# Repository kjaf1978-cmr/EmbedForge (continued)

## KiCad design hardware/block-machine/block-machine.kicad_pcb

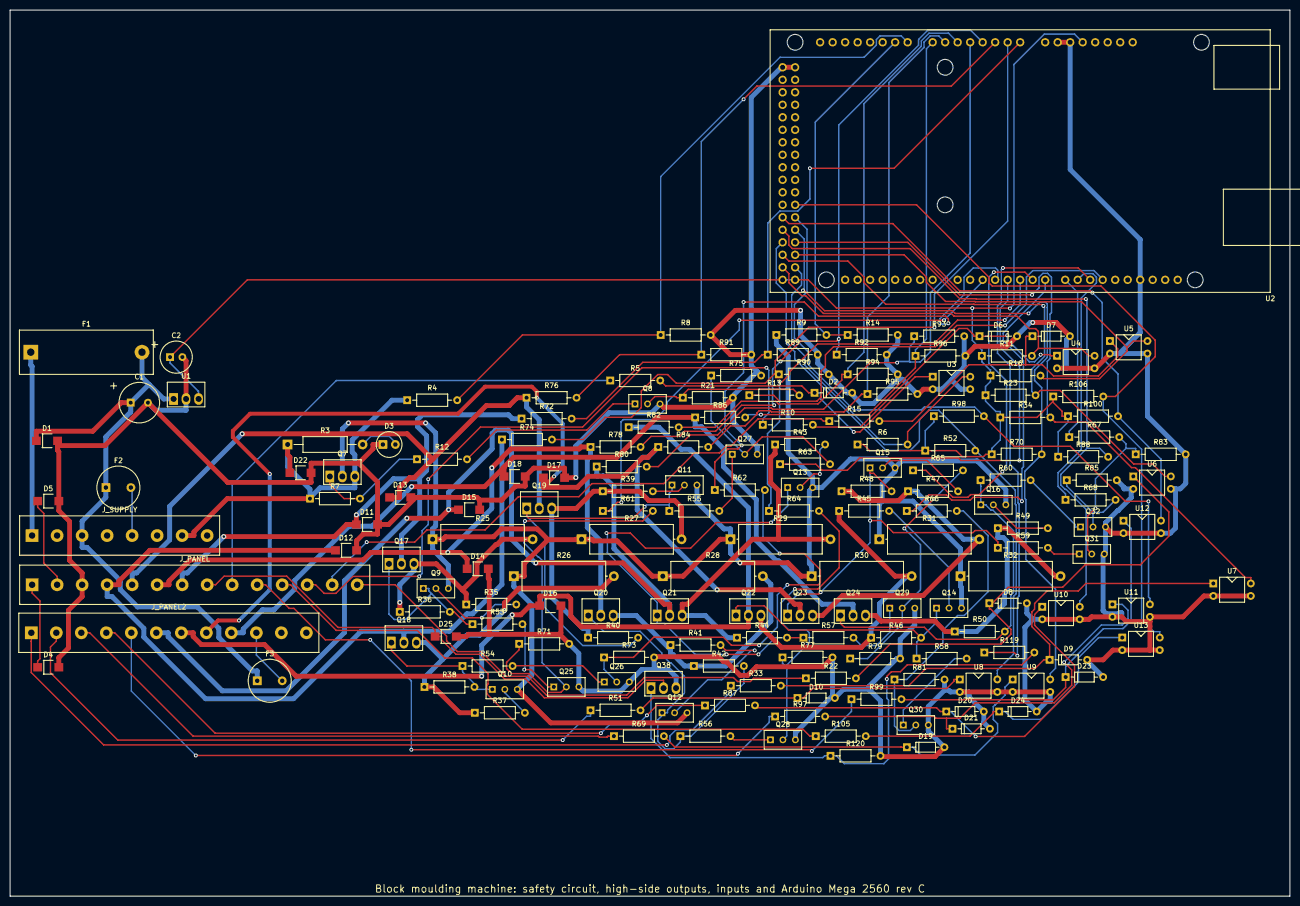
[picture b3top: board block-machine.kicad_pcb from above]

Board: 2 copper layers, 260.0 x 180.0 mm, 170 parts (0 on the bottom side), 117 nets.

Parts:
C1: 22u; CP_Radial_D8
C2: 22u; CP_Radial_D6.3
D1, D25: SMAJ33A; D_SMA
D2, D6, D7, D8, D9, D10, D19, D20, D21, D23, D24: 1N4148; D_DO-35
D3: green; LED_D5.0
D4, D5, D11, D12, D13, D14, D15, D16, D17, D18, D22: SMAJ33CA; D_SMA
F1: 8; Fuseholder_5x20
F2: 2; F_TR5
F3: 1; F_TR5
J_PANEL: to the panel; TerminalBlock_1x14
J_PANEL2: to the panel; TerminalBlock_1x12
J_SUPPLY: supplies to the panel; TerminalBlock_1x8
Q7: IRF4905; TO-220_Vertical
Q8, Q25, Q26, Q27, Q28, Q29, Q30, Q31, Q32: BC547B; TO-92_Wide
Q9, Q10, Q11, Q12, Q13, Q14, Q15, Q16: BC557B; TO-92_Wide
Q17, Q18, Q19, Q20, Q21, Q22, Q23, Q24: IRF9540N; TO-220_Vertical
Q38: IRLZ44N; TO-220_Vertical
R3: 2.2k; R_Axial_0309
R4, R9, R21, R71, R72, R73, R74, R75, R76, R77, R78, R79, R80, R81, R82, R83, R84, R85, R86: 47k; R_Axial_0207
R5, R10, R15, R22, R33, R51, R69, R87, R97, R99, R105: 4.7k; R_Axial_0207
R6, R7, R8, R11, R12, R13, R14, R16, R23, R34, R36, R38, R40, R42, R44, R46, R48, R50, R52, R53, R54, R55, R56, R57, R58, R59, R60, R61, R62, R63, R64, R65, R66, R67, R68, R70, R88, R89, R90, R91, R92, R93, R94, R95, R96, R98, R100, R106, R120: 10k; R_Axial_0207
R25, R26, R27, R28, R29, R30, R31, R32: 0.33; R_Axial_P20
R35, R37, R39, R41, R43, R45, R47, R49, R119: 100; R_Axial_0207
U1: R-78E5.0-1.0; TO-220_Vertical
U2: Arduino Mega 2560; Arduino_Mega2560_Shield
U3, U4, U5, U6, U7, U8, U9, U10, U11, U12, U13: PC817; DIP-4

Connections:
BEN: Q8.2, R13.2, R21.1
BIM: Q10.2, R37.2
BIP: Q9.2, R35.2
BIS1: Q13.2, R43.2
BIS2: Q14.2, R45.2
BIS3: Q15.2, R47.2
BIS4: Q16.2, R49.2
BIV1: Q11.2, R39.2
BIV2: Q12.2, R41.2
BM: Q26.2, R62.2, R73.1
BP: Q25.2, R61.2, R71.1
BS1: Q29.2, R65.2, R79.1
BS2: Q30.2, R66.2, R81.1
BS3: Q31.2, R67.2, R83.1
BS4: Q32.2, R68.2, R85.1
BV1: Q27.2, R63.2, R75.1
BV2: Q28.2, R64.2, R77.1
C1: D4.1, J_PANEL.1
C2: D5.1, J_PANEL.2
DEN: Q8.1, R12.2
DM: Q26.1, R54.2
DP: Q25.1, R53.2
DS1: Q29.1, R57.2
DS2: Q30.1, R58.2
DS3: Q31.1, R59.2
DS4: Q32.1, R60.2
DV1: Q27.1, R55.2
DV2: Q28.1, R56.2
ENABLE: R13.1, U2.D11
GEN: Q7.1, R7.2, R12.1
GL: Q38.1, R119.2, R120.1
GM: Q10.1, Q18.1, R38.2, R54.1
GND: C1.2, C2.2, D1.2, D2.2, D3.1, D4.2, D5.2, D6.2, D7.2, D8.2, D9.2, D10.2, D11.2, D12.2, D13.2, D14.2, D15.2, D16.2, D17.2, D18.2, D19.2, D20.2, D21.2, D22.2, D23.2, D24.2, D25.2, J_PANEL.3, Q8.3, Q25.3, Q26.3, Q27.3, Q28.3, Q29.3, Q30.3, Q31.3, Q32.3, Q38.3, R8.2, R14.2, R21.2, R71.2, R73.2, R75.2, R77.2, R79.2, R81.2, R83.2, R85.2, R89.2, R90.2, R91.2, R92.2, R93.2, R94.2, R95.2, R96.2, R120.2, U1.2, U2.GND1, U2.GND2, U2.GND3, U2.GND4, U2.GND5, U3.2, U3.3, U4.2, U4.3, U5.2, U5.3, U6.2, U6.3, U7.2, U7.3, U8.2, U8.3, U9.2, U9.3, U10.2, U10.3, U11.2, U11.3, U12.2, U12.3, U13.2, U13.3
GP: Q9.1, Q17.1, R36.2, R53.1
GS1: Q13.1, Q21.1, R44.2, R57.1
GS2: Q14.1, Q22.1, R46.2, R58.1
GS3: Q15.1, Q23.1, R48.2, R59.1
GS4: Q16.1, Q24.1, R50.2, R60.1
GV1: Q11.1, Q19.1, R40.2, R55.1
GV2: Q12.1, Q20.1, R42.2, R56.1
HSM: Q18.3, R26.2, R37.1, R38.1
HSP: Q17.3, R25.2, R35.1, R36.1
HSS1: Q21.3, R29.2, R43.1, R44.1
HSS2: Q22.3, R30.2, R45.1, R46.1
HSS3: Q23.3, R31.2, R47.1, R48.1
HSS4: Q24.3, R32.2, R49.1, R50.1
HSV1: Q19.3, R27.2, R39.1, R40.1
HSV2: Q20.3, R28.2, R41.1, R42.1
IN1: R6.2, U2.D22, U3.4
IN2: R11.2, U2.D23, U4.4
IN3: R16.2, U2.D24, U5.4
IN4: R23.2, U2.D25, U6.4
IN5: R34.2, U2.D26, U7.4
IN6: R52.2, U2.D27, U8.4
IN7: R70.2, U2.D28, U9.4
IN8: R88.2, U2.D29, U10.4
IN9: R98.2, U2.D30, U11.4
IN10: R100.2, U2.D31, U12.4
IN11: R106.2, U2.D32, U13.4
KMMA: D12.1, J_PANEL.4, Q18.2, R74.1
KMV1A: D13.1, J_PANEL.5, Q19.2, R76.1
KMV2A: D14.1, J_PANEL.6, Q20.2, R78.1
KPA: D11.1, J_PANEL.7, Q17.2, R72.1
LAMP: R119.1, U2.D10
LMP: D25.1, J_PANEL.8, Q38.2
LSA: D3.2, R3.2
MIXER: R62.1, U2.D3
PUMP: R61.1, U2.D2
PX1: J_PANEL.9, R5.1
PX2: J_PANEL.12, R10.1
PX3: J_PANEL.13, R15.1
PX4: J_PANEL.14, R22.1
PX5: J_PANEL2.1, R33.1
PX6: J_PANEL2.2, R51.1
PX7: J_PANEL2.3, R69.1
PX8: J_PANEL2.4, R87.1
PX9: J_PANEL2.5, R97.1
PX10: J_PANEL.10, R99.1
PX11: J_PANEL.11, R105.1
PXA1: D2.1, R5.2, U3.1
PXA2: D6.1, R10.2, U4.1
PXA3: D7.1, R15.2, U5.1
PXA4: D8.1, R22.2, U6.1
PXA5: D9.1, R33.2, U7.1
PXA6: D10.1, R51.2, U8.1
PXA7: D19.1, R69.2, U9.1
PXA8: D20.1, R87.2, U10.1
PXA9: D21.1, R97.2, U11.1
PXA10: D23.1, R99.2, U12.1
PXA11: D24.1, R105.2, U13.1
RBEN: R9.2, R14.1, U2.A9
RBM: R74.2, R90.1, U2.A1
RBP: R72.2, R89.1, U2.A0
RBS1: R80.2, R93.1, U2.A4
RBS2: R82.2, R94.1, U2.A5
RBS3: R84.2, R95.1, U2.A6
RBS4: R86.2, R96.1, U2.A7
RBV1: R76.2, R91.1, U2.A2
RBV2: R78.2, R92.1, U2.A3
SRS: R4.2, R8.1, U2.A8
SV1: D15.1, J_PANEL2.6, Q21.2, R80.1
SV2: D16.1, J_PANEL2.7, Q22.2, R82.1
SV3: D17.1, J_PANEL2.8, Q23.2, R84.1
SV4: D18.1, J_PANEL2.9, Q24.2, R86.1
V5: C2.1, R6.1, R11.1, R16.1, R23.1, R34.1, R52.1, R70.1, R88.1, R98.1, R100.1, R106.1, U1.3, U2.5V1, U2.5V2, U2.5V3
V24: F1.1, J_SUPPLY.1
V24F: C1.1, D1.1, F1.2, F2.1, F3.1, J_SUPPLY.3, U1.1
V24I: F2.2, J_SUPPLY.5
V24K: F3.2, J_PANEL2.10
V24O: Q7.2, Q9.3, Q10.3, Q11.3, Q12.3, Q13.3, Q14.3, Q15.3, Q16.3, R9.1, R25.1, R26.1, R27.1, R28.1, R29.1, R30.1, R31.1, R32.1
V24S: D22.1, J_SUPPLY.7, Q7.3, R3.1, R4.1, R7.1
VALVE1: R65.1, U2.D6
VALVE2: R66.1, U2.D7
VALVE3: R67.1, U2.D8
VALVE4: R68.1, U2.D9
VIB1: R63.1, U2.D4
VIB2: R64.1, U2.D5

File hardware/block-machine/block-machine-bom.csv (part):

"on this board","qty","references","part","value","details","footprint","MPN","maker","distributors (order numbers)","unit EUR","total EUR","price basis"
"yes","1","C1","Electrolytic capacitor","22 µF","voltage rating 50 V","CP_Radial_D8","22uF 50 V 105 °C (e.g. Panasonic FC series)","Panasonic / Nichicon","any distributor (radial)","0.10","0.10","estimate"
"yes","1","C2","Electrolytic capacitor","22 µF","voltage rating 16 V","CP_Radial_D6.3","22uF 16 V 105 °C (e.g. Panasonic FC series)","Panasonic / Nichicon","any distributor (radial)","0.10","0.10","estimate"
"yes","2","D1 D25","TVS diode","SMAJ33A","","D_SMA","SMAJ33A","Littelfuse","LCSC; Mouser","0.20","0.40","estimate"
"yes","11","D2 D6 D7 D8 D9 D10 D19 D20 D21 D23 D24","Diode","1N4148","","D_DO-35","1N4148","various","any distributor (DO-35)","0.06","0.66","estimate"
"yes","1","D3","LED","green","","LED_D5.0","5 mm green LED, 20 mA","Kingbright (e.g. L-53GD)","any distributor (5 mm LED)","0.12","0.12","estimate"
"yes","11","D4 D5 D11 D12 D13 D14 D15 D16 D17 D18 D22","TVS diode","SMAJ33CA","","D_SMA","SMAJ33CA","Littelfuse","LCSC; Mouser","0.22","2.42","estimate"
"yes","1","F1","Fuse","8 A","cold resistance 10 mΩ","Fuseholder_5x20","FST 5×20 T 8 A (Schurter 0034.31xx series) + PCB holder 0031.8201","Schurter","Bürklin (holder) 46G6020","1.20","1.20","estimate"
"yes","1","F2","Fuse","2 A","cold resistance 50 mΩ","F_TR5","FST 5×20 T 2 A (Schurter 0034.31xx series) + PCB holder 0031.8201","Schurter","Bürklin (holder) 46G6020","1.20","1.20","estimate"
"yes","1","F3","Fuse","1 A","cold resistance 200 mΩ","F_TR5","FST 5×20 T 1 A (Schurter 0034.31xx series) + PCB holder 0031.8201","Schurter","Bürklin (holder) 46G6020","1.20","1.20","estimate"
"yes","1","Q7","P-channel MOSFET","IRF4905","","TO-220_Vertical","IRF4905PBF","Infineon","Mouser; RS","1.60","1.60","estimate"
"yes","9","Q8 Q25 Q26 Q27 Q28 Q29 Q30 Q31 Q32","NPN transistor","BC547B","","TO-92_Wide","BC547B","onsemi","any distributor (TO-92)","0.10","0.90","estimate"
"yes","8","Q9 Q10 Q11 Q12 Q13 Q14 Q15 Q16","PNP transistor","BC557B","","TO-92_Wide","BC557B","onsemi","any distributor (TO-92)","0.10","0.80","estimate"
"yes","8","Q17 Q18 Q19 Q20 Q21 Q22 Q23 Q24","P-channel MOSFET","IRF9540N","","TO-220_Vertical","IRF9540NPBF","Infineon","Mouser; RS","1.10","8.80","estimate"
"yes","1","Q38","N-channel MOSFET","IRLZ44N","","TO-220_Vertical","IRLZ44NPBF","Infineon","Mouser; LCSC C38774","1.85","1.85","live"
"yes","1","R3","Resistor","2.2 kΩ","power rating 500 mW","R_Axial_0309","metal film 2.2kΩ 0.6 W, 1 %, 50 ppm/K (e.g. Vishay MBB0207)","Vishay / Yageo","any distributor (0207 1 %)","0.08","0.08","estimate"
"yes","19","R4 R9 R21 R71 R72 R73 R74 R75 R76 R77 R78 R79 R80 R81 R82 R83 R84 R85 R86","Resistor","47 kΩ","power rating 250 mW","R_Axial_0207","metal film 47kΩ 0.6 W, 1 %, 50 ppm/K (e.g. Vishay MBB0207)","Vishay / Yageo","any distributor (0207 1 %)","0.08","1.52","estimate"
"yes","11","R5 R10 R15 R22 R33 R51 R69 R87 R97 R99 R105","Resistor","4.7 kΩ","power rating 250 mW","R_Axial_0207","metal film 4.7kΩ 0.6 W, 1 %, 50 ppm/K (e.g. Vishay MBB0207)","Vishay / Yageo","any distributor (0207 1 %)","0.08","0.88","estimate"
"yes","49","R6 R7 R8 R11 R12 R13 R14 R16 R23 R34 R36 R38 R40 R42 R44 R46 R48 R50 R52 R53 R54 R55 R56 R57 R58 R59 R60 R61 R62 R63 R64 R65 R66 R67 R68 R70 R88 R89 R90 R91 R92 R93 R94 R95 R96 R98 R100 R106 R120","Resistor","10 kΩ","power rating 250 mW","R_Axial_0207","metal film 10kΩ 0.6 W, 1 %, 50 ppm/K (e.g. Vishay MBB0207)","Vishay / Yageo","any distributor (0207 1 %)","0.08","3.92","estimate"
"yes","8","R25 R26 R27 R28 R29 R30 R31 R32","Resistor","330 mΩ","power rating 2 W","R_Axial_P20","metal oxide 0.33Ω 3 W (e.g. Vishay PR03)","Vishay / Yageo","any distributor (axial 3 W)","0.25","2.00","estimate"
"yes","9","R35 R37 R39 R41 R43 R45 R47 R49 R119","Resistor","100 Ω","power rating 250 mW","R_Axial_0207","metal film 100Ω 0.6 W, 1 %, 50 ppm/K (e.g. Vishay MBB0207)","Vishay / Yageo","any distributor (0207 1 %)","0.08","0.72","estimate"
"yes","1","U1","Voltage regulator","R-78E5.0-1.0","","TO-220_Vertical","R-78E5.0-1.0","Recom","Mouser 919-R-78E5.0-1.0; Farnell","4.20","4.20","estimate"
"yes","1","U2","Microcontroller module (Arduino Mega 2560, 5 V)","Arduino Mega 2560","","Arduino_Mega2560_Shield","A000067 (Arduino Mega 2560 Rev3)","Arduino","Arduino Store; RS","42.00","42.00","estimate"
"yes","11","U3 U4 U5 U6 U7 U8 U9 U10 U11 U12 U13","Optocoupler","PC817","","DIP-4","PC817X1NSZ1B","Sharp","any distributor (DIP-4)","0.30","3.30","estimate"
"no","2","K1 K4","Safety relay (E-stop / guard)","3SK1111-1AB30","","","3SK1111-1AB30","Siemens","RS; Automation24","135.00","270.00","estimate"
"no","2","K2 K3","Contactor","9 A, coil 24 V DC, + aux block 1 NO + 1 NC","","","3RT2016-1BB42 + 3RH2911-1HA11","Siemens","RS; Automation24","55.00","110.00","estimate"
"no","2","K5 K6","Contactor","18 A, coil 24 V DC","","","3RT2026-1BB40 + 3RH2911-1HA11","Siemens","RS; Automation24","75.00","150.00","estimate"
"no","3","K7 K8 K9","Contactor","9 A, coil 24 V DC","","","3RT2016-1BB42 + 3RH2911-1HA11","Siemens","RS; Automation24","55.00","165.00","estimate"
"no","1","Q33","Circuit breaker 3-pole","C32 A","","","S203-C32 + S2C-H6R handle lock","ABB","electrical wholesale","75.00","75.00","estimate"
"no","1","Q34","Circuit breaker 3-pole","M16 A","","","3RV2021-4AA10 + 3RV2901-1E","Siemens","RS; Automation24","78.00","78.00","estimate"
"no","1","Q35","Circuit breaker 3-pole","M6 A","","","3RV2011-1HA10 + 3RV2901-1E","Siemens","RS; Automation24","62.00","62.00","estimate"
"no","2","Q36 Q37","Circuit breaker 3-pole","M4 A","","","3RV2011-1EA10 + 3RV2901-1E","Siemens","RS; Automation24","60.00","120.00","estimate"
"no","54","X1 X2 X3 X4 X5 X6 X7 X8 X9 X10 X11 X12 X13 X14 X15 X16 X17 X18 X19 X20 X21 X22 X23 X24 X25 X26 X27 X28 X29 X30 X31 X32 X33 X34 X35 X36 X37 X38 X39 X40 X41 X42 X43 X44 X45 X46 X47 X48 X49 X50 X51 X52 X53 X54","Screw terminal","5.08 mm, 1 pole","functions: X1 +24 V (panel supply), X2 0 V, X3 0 V – PE bond (the one point), X4 E-stop channel 1 (NC): S11, X5 E-stop channel 1: S12, X6 proximity sensor 1: mould up (PNP out), X7 E-stop channel 2 (NC): S21, X8 E-stop channel 2: S22, X9 proximity sensor 2: mould down (PNP out), X10 guard channel 1 (NC): S11, X11 guard channel 1: S12, X12 guard channel 2 (NC): S21, X13 guard channel 2: S22, X14 proximity sensor 3: tamper up (PNP out), X15 RESET block a (NO): S33 of the E-stop relay, X16 RESET block a, X17 RESET block b (NO): S33 of the guard relay, X18 proximity sensor 4: tamper down (PNP out), X19 RESET block b, X20 proximity sensor 5: feeder home (PNP out), X21 proximity sensor 6: pallet in place (PNP out), X22 START (NO, 24 V), X23 STOP (NC, 24 V), X24 valve 1 (tamper down) +, X25 valve 1 (tamper down) −, X26 valve 2 (tamper up) +, X27 valve 2 (tamper up) −, X28 valve 3 (mould up) +, X29 valve 3 (mould up) −, X30 valve 4 (mould down) +, X31 valve 4 (mould down) −, X32 pressure switch (NO, closes at the working pressure), X33 supply L1 (400 V, 3 phases), X34 supply L2, X35 oil temperature switch (NC, opens when hot), X36 supply L3, X37 motor breakers healthy (their auxiliary NO contacts in series), X38 pump motor U, X39 pump motor V, X40 pump motor W, X41 mixer / feeder 3 kW: U, X42 mixer / feeder 3 kW: V, X43 mixer / feeder 3 kW: W, X44 vibrator 1, 1.5 kW: U, X45 vibrator 1, 1.5 kW: V, X46 vibrator 1, 1.5 kW: W, X47 vibrator 2, 1.5 kW: U, X48 vibrator 2, 1.5 kW: V, X49 vibrator 2, 1.5 kW: W, X50 field +24 V (sensors, buttons, switches; F2), X51 field +24 V, X52 field 0 V, X53 lamp READY / FAULT +24 V, X54 lamp READY / FAULT −","","MKDS 1,5/ 2-5,08 (2 poles per block)","Phoenix Contact","RS 193-0564","0.40","21.60","estimate"

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
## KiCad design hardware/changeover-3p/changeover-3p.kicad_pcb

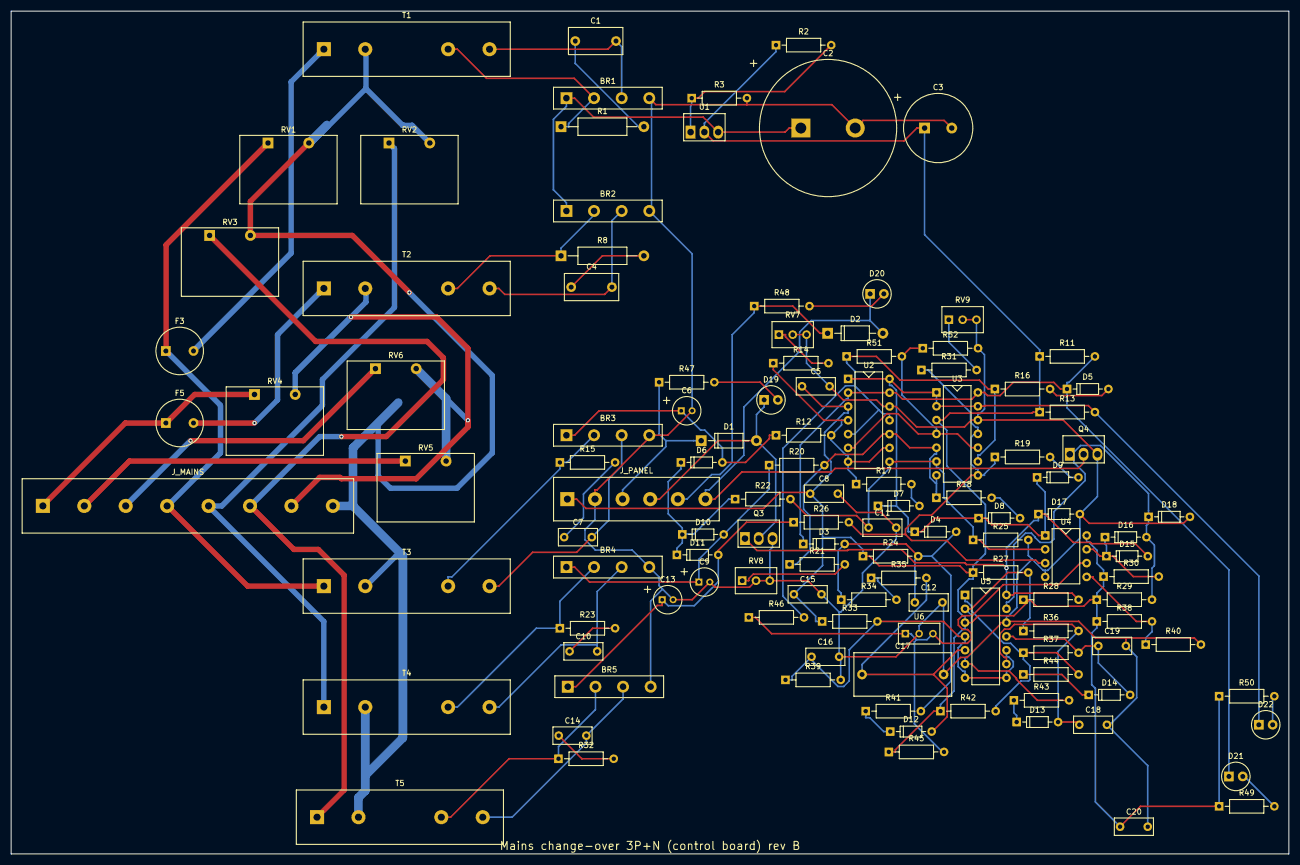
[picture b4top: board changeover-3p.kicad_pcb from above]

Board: 2 copper layers, 235.0 x 155.0 mm, 119 parts (0 on the bottom side), 72 nets.

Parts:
BR1, BR2, BR3, BR4, BR5: DB107; Bridge_Inline_4
C1, C4: 1u; C_Film_P7.5
C2: 2200u; CP_SnapIn_D25
C3: 100u; CP_Radial_D12.5
C5, C7, C8, C10, C11, C14, C15, C16, C20: 100n; C_Disc_5.08
C6, C9, C13: 4.7u; CP_Radial_D5
C12: 1u; C_Disc_5.08
C17: 10u; C_Film_P15
C18, C19: 680n; C_Disc_5.08
D1, D2: 1N4007; D_DO-41
D3, D4, D5, D6, D7, D8, D9, D10, D11, D12, D13, D14, D15, D16: 1N4148; D_DO-35
D17, D18: BZX55C12; D_DO-35
D19: green; LED_D5.0
D20: yellow; LED_D5.0
D21, D22: red; LED_D5.0
F3, F5: 0.2; F_TR5
J_MAINS: mains to the panel; TerminalBlock_1x8_P7.62
J_PANEL: to the panel; TerminalBlock_1x6
Q3, Q4: IRLZ44N; TO-220_Vertical
R1, R8: 47; R_Axial_0309
R2: 240; R_Axial_0207
R3: 4.42k; R_Axial_0207
R11, R13, R24, R27, R28, R29, R30, R33, R39, R40, R42: 10k; R_Axial_0207
R12, R20, R26, R38: 68k; R_Axial_0207
R14, R21, R31: 6.8k; R_Axial_0207
R15, R23, R32: 220; R_Axial_0207
R16: 33k; R_Axial_0207
R17, R18, R19, R25: 100k; R_Axial_0207
R22: 768k; R_Axial_0207
R34, R35: 750k; R_Axial_0207
R36, R37: 1M; R_Axial_0207
R41, R43, R44, R47, R48, R49, R50: 4.7k; R_Axial_0207
R45: 3.3k; R_Axial_0207
R46: 2.1k; R_Axial_0207
R51: 4.22k; R_Axial_0207
R52: 12.1k; R_Axial_0207
RV1, RV2, RV3, RV4, RV5, RV6: TMOV14RP300E; TMOV_14
RV7, RV8, RV9: 5k; Pot_Trimmer_3
T1, T2: 0.13; Transformer_Wires_P7.62
T3, T4, T5: 0.052; Transformer_Wires_P7.62
U1: LM317HV; TO-220_Vertical
U2, U3, U5: LM339; DIP-14
U4: LM393; DIP-8
U6: TL431; TO-92_Wide

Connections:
+24V: C3.1, C5.1, C8.1, C15.1, C20.1, J_PANEL.1, R2.1, R11.1, R13.1, R24.1, R27.1, R28.1, R29.1, R30.1, R33.1, R38.1, R42.1, R45.1, R49.1, R50.1, U1.2, U2.3, U3.3, U4.8, U5.3
A4A: BR1.2, R1.1, T1.3
A4B: BR1.3, C1.2, T1.4
A5A: BR2.2, R8.1, T2.3
A5B: BR2.3, C4.2, T2.4
ADJ: R2.2, R3.1, U1.1
B1F: F5.1, J_MAINS.1, RV4.1
B2F: J_MAINS.2, RV5.1
B3F: J_MAINS.3, RV6.1
CDT1N: C18.1, D13.2, R36.2, U5.9
CDT2N: C19.1, D14.2, R37.2, U5.11
DTS1: D13.1, R43.1
DTS2: D14.1, R44.1
GND: BR1.4, BR2.4, BR3.4, BR4.4, BR5.4, C2.2, C3.2, C5.2, C6.2, C8.2, C9.2, C11.2, C12.2, C13.2, C15.2, C16.2, C17.2, C18.2, C19.2, C20.2, D17.2, D18.2, J_PANEL.2, Q3.3, Q4.3, R3.2, R25.2, R39.2, R40.2, R52.2, RV7.2, RV7.3, RV8.2, RV8.3, RV9.2, RV9.3, U2.12, U3.12, U4.4, U5.12, U6.2
HOV: D5.2, R16.2
HU1: D7.2, R17.2
HU2: D8.2, R18.2
HU3: D9.2, R19.2
K1A: D1.1, J_PANEL.3, R47.1
K1C: D1.2, D19.1, J_PANEL.4, Q3.2
K1EN: D15.2, D17.1, Q3.1, R28.2, U5.14
K2A: D2.1, J_PANEL.5, R48.1
K2C: D2.2, D20.1, J_PANEL.6, Q4.2
K2EN: D16.2, D18.1, Q4.1, R29.2, U5.13
L1F: F3.1, J_MAINS.4, RV1.1, T3.1
L2F: J_MAINS.5, RV2.1, T4.1
L3F: J_MAINS.6, RV3.1, T5.1
LF4: F3.2, T1.1
LF5: F5.2, T2.1
LK1A: D19.2, R47.2
LK2A: D20.2, R48.2
LOVA: D21.2, R49.2
LUVA: D22.2, R50.2
NBQ: J_MAINS.7, RV4.2, RV5.2, RV6.2, T2.2
NMQ: J_MAINS.8, RV1.2, RV2.2, RV3.2, T1.2, T3.2, T4.2, T5.2
ODS: D12.1, R41.1
OK: C12.1, D3.2, D4.2, R24.2, R34.1, R41.2
OKC: C17.1, D12.2, R35.2, U5.5
OKD: R27.2, R36.1, R43.2, U5.2, U5.6
OKDN: R37.1, R42.2, R44.2, U5.1
ORD: R34.2, R35.1
OVN: D3.1, D5.1, D21.1, R11.2, U2.2, U2.13, U3.14
S1: R12.2, R14.1, R17.1, U2.4, U2.7, U2.9
S2: R18.1, R20.2, R21.1, U2.10, U3.5, U3.7
S3: R19.1, R26.2, R31.1, U3.8, U3.11, U4.3
SA1: BR3.2, R15.1, T3.3
SA2: BR4.2, R23.1, T4.3
SA3: BR5.2, R32.1, T5.3
SA4X: C1.1, R1.2
SA5X: C4.1, R8.2
SB1: BR3.3, C7.2, T3.4
SB2: BR4.3, C10.2, T4.4
SB3: BR5.3, C14.2, T5.4
SN1: C7.1, R15.2
SN2: C10.1, R23.2
SN3: C14.1, R32.2
ST1: R14.2, RV7.1
ST2: R21.2, RV8.1
ST3: R31.2, RV9.1
UVL: D15.1, D16.1, R30.2, U4.7
UVN: D4.1, D7.1, D8.1, D9.1, D22.1, R13.2, U2.1, U2.14, U3.1, U3.2, U3.13, U4.1
V24S: R38.2, R40.1, U4.5
VAS: C11.1, R22.2, R25.1, U2.8, U3.6, U4.2
VHI: R16.1, R46.2, R51.1, U2.5, U2.11, U3.9
VLO: R51.2, R52.1, U2.6, U3.4, U3.10
VMAX: D6.1, D10.1, D11.1, R22.1
VRAW: BR1.1, BR2.1, C2.1, U1.3
VREF: R45.2, R46.1, U4.6, U6.1, U6.3
VSR1: BR3.1, C6.1, D6.2, R12.1
VSR2: BR4.1, C9.1, D10.2, R20.1
VSR3: BR5.1, C13.1, D11.2, R26.1
VTH: C16.1, R33.2, R39.1, U5.4, U5.7, U5.8, U5.10

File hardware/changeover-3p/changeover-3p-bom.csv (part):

"on this board","qty","references","part","value","details","footprint","MPN","maker","distributors (order numbers)","unit EUR","total EUR","price basis"
"yes","5","BR1 BR2 BR3 BR4 BR5","Bridge rectifier","DB107","","Bridge_Inline_4","DB107","various","any distributor (DIP-4)","0.30","1.50","estimate"
"yes","2","C1 C4","Capacitor","1 µF","voltage rating 100 V","C_Film_P7.5","MKT film 1uF 100 V (e.g. WIMA MKS4, TDK B32529)","WIMA / TDK","any distributor (film)","0.35","0.70","estimate"
"yes","1","C2","Electrolytic capacitor","2.2 mF","voltage rating 63 V","CP_SnapIn_D25","2200uF 63 V 105 °C low-ESR long life (series e.g. Nichicon UHW, Panasonic FC/FR)","Nichicon / Panasonic","Future Electronics / Mouser","3.20","3.20","estimate"
"yes","1","C3","Electrolytic capacitor","100 µF","voltage rating 50 V","CP_Radial_D12.5","100uF 50 V 105 °C (e.g. Panasonic FC series)","Panasonic / Nichicon","any distributor (radial)","0.25","0.25","estimate"
"yes","6","C5 C8 C11 C15 C16 C20","Capacitor","100 nF","voltage rating 50 V","C_Disc_5.08","ceramic X7R or MKT 100nF 50 V, 5.08 mm","KEMET / Vishay","any distributor (5.08 mm)","0.12","0.72","estimate"
"yes","3","C6 C9 C13","Electrolytic capacitor","4.7 µF","voltage rating 50 V","CP_Radial_D5","4.7uF 50 V 105 °C (e.g. Panasonic FC series)","Panasonic / Nichicon","any distributor (radial)","0.10","0.30","estimate"
"yes","3","C7 C10 C14","Capacitor","100 nF","voltage rating 63 V","C_Disc_5.08","ceramic X7R or MKT 100nF 63 V, 5.08 mm","KEMET / Vishay","any distributor (5.08 mm)","0.12","0.36","estimate"
"yes","1","C12","Capacitor","1 µF","voltage rating 50 V","C_Disc_5.08","MKT film 1uF 50 V (e.g. WIMA MKS4, TDK B32529)","WIMA / TDK","any distributor (film)","0.35","0.35","estimate"
"yes","1","C17","Capacitor","10 µF","voltage rating 50 V","C_Film_P15","MKT film 10uF 50 V (e.g. WIMA MKS4, TDK B32529)","WIMA / TDK","any distributor (film)","0.80","0.80","estimate"
"yes","2","C18 C19","Capacitor","680 nF","voltage rating 50 V","C_Disc_5.08","MKT film 680nF 50 V, 5.08 mm (e.g. WIMA MKS2, TDK B32529)","WIMA / TDK","any distributor (film)","0.25","0.50","estimate"
"yes","2","D1 D2","Diode","1N4007","","D_DO-41","1N4007","various","any distributor (DO-41)","0.10","0.20","estimate"
"yes","14","D3 D4 D5 D6 D7 D8 D9 D10 D11 D12 D13 D14 D15 D16","Diode","1N4148","","D_DO-35","1N4148","various","any distributor (DO-35)","0.06","0.84","estimate"
"yes","2","D17 D18","Zener diode","BZX55C12","","D_DO-35","BZX55C12","Vishay","any distributor (DO-35)","0.08","0.16","estimate"
"yes","1","D19","LED","green","","LED_D5.0","5 mm green LED, 20 mA","Kingbright (e.g. L-53GD)","any distributor (5 mm LED)","0.12","0.12","estimate"
"yes","1","D20","LED","yellow","","LED_D5.0","5 mm yellow LED, 20 mA","Kingbright (e.g. L-53YD)","any distributor (5 mm LED)","0.12","0.12","estimate"
"yes","2","D21 D22","LED","red","","LED_D5.0","5 mm red LED, 20 mA","Kingbright (e.g. L-53ID)","any distributor (5 mm LED)","0.12","0.24","estimate"
"yes","2","F3 F5","Fuse","200 mA","cold resistance 2 Ω","F_TR5","FST 5×20 T 0.2 A (Schurter 0034.31xx series) + PCB holder 0031.8201","Schurter","Bürklin (holder) 46G6020","1.20","2.40","estimate"
"yes","2","Q3 Q4","N-channel MOSFET","IRLZ44N","","TO-220_Vertical","IRLZ44NPBF","Infineon","Mouser; LCSC C38774","1.85","3.70","live"
"yes","2","R1 R8","Resistor","47 Ω","power rating 500 mW","R_Axial_0309","metal film 47Ω 0.6 W, 1 %, 50 ppm/K (e.g. Vishay MBB0207)","Vishay / Yageo","any distributor (0207 1 %)","0.08","0.16","estimate"
"yes","1","R2","Resistor","240 Ω","power rating 250 mW","R_Axial_0207","metal film 240Ω 0.6 W, 1 %, 50 ppm/K (e.g. Vishay MBB0207)","Vishay / Yageo","any distributor (0207 1 %)","0.08","0.08","estimate"
"yes","1","R3","Resistor","4.42 kΩ","power rating 250 mW","R_Axial_0207","metal film 4.42kΩ 0.6 W, 1 %, 50 ppm/K (e.g. Vishay MBB0207)","Vishay / Yageo","any distributor (0207 1 %)","0.08","0.08","estimate"
"yes","11","R11 R13 R24 R27 R28 R29 R30 R33 R39 R40 R42","Resistor","10 kΩ","power rating 250 mW","R_Axial_0207","metal film 10kΩ 0.6 W, 1 %, 50 ppm/K (e.g. Vishay MBB0207)","Vishay / Yageo","any distributor (0207 1 %)","0.08","0.88","estimate"
"yes","4","R12 R20 R26 R38","Resistor","68 kΩ","power rating 250 mW","R_Axial_0207","metal film 68kΩ 0.6 W, 1 %, 50 ppm/K (e.g. Vishay MBB0207)","Vishay / Yageo","any distributor (0207 1 %)","0.08","0.32","estimate"
"yes","3","R14 R21 R31","Resistor","6.8 kΩ","power rating 250 mW","R_Axial_0207","metal film 6.8kΩ 0.6 W, 1 %, 50 ppm/K (e.g. Vishay MBB0207)","Vishay / Yageo","any distributor (0207 1 %)","0.08","0.24","estimate"
"yes","3","R15 R23 R32","Resistor","220 Ω","power rating 250 mW","R_Axial_0207","metal film 220Ω 0.6 W, 1 %, 50 ppm/K (e.g. Vishay MBB0207)","Vishay / Yageo","any distributor (0207 1 %)","0.08","0.24","estimate"
"yes","1","R16","Resistor","33 kΩ","power rating 250 mW","R_Axial_0207","metal film 33kΩ 0.6 W, 1 %, 50 ppm/K (e.g. Vishay MBB0207)","Vishay / Yageo","any distributor (0207 1 %)","0.08","0.08","estimate"
"yes","4","R17 R18 R19 R25","Resistor","100 kΩ","power rating 250 mW","R_Axial_0207","metal film 100kΩ 0.6 W, 1 %, 50 ppm/K (e.g. Vishay MBB0207)","Vishay / Yageo","any distributor (0207 1 %)","0.08","0.32","estimate"
"yes","1","R22","Resistor","768 kΩ","power rating 250 mW","R_Axial_0207","metal film 768kΩ 0.6 W, 1 %, 50 ppm/K (e.g. Vishay MBB0207)","Vishay / Yageo","any distributor (0207 1 %)","0.08","0.08","estimate"
"yes","2","R34 R35","Resistor","750 kΩ","power rating 250 mW","R_Axial_0207","metal film 750kΩ 0.6 W, 1 %, 50 ppm/K (e.g. Vishay MBB0207)","Vishay / Yageo","any distributor (0207 1 %)","0.08","0.16","estimate"
"yes","2","R36 R37","Resistor","1 MΩ","power rating 250 mW","R_Axial_0207","metal film 1MΩ 0.6 W, 1 %, 50 ppm/K (e.g. Vishay MBB0207)","Vishay / Yageo","any distributor (0207 1 %)","0.08","0.16","estimate"
"yes","7","R41 R43 R44 R47 R48 R49 R50","Resistor","4.7 kΩ","power rating 250 mW","R_Axial_0207","metal film 4.7kΩ 0.6 W, 1 %, 50 ppm/K (e.g. Vishay MBB0207)","Vishay / Yageo","any distributor (0207 1 %)","0.08","0.56","estimate"
"yes","1","R45","Resistor","3.3 kΩ","power rating 250 mW","R_Axial_0207","metal film 3.3kΩ 0.6 W, 1 %, 50 ppm/K (e.g. Vishay MBB0207)","Vishay / Yageo","any distributor (0207 1 %)","0.08","0.08","estimate"
"yes","1","R46","Resistor","2.1 kΩ","power rating 250 mW","R_Axial_0207","metal film 2.1kΩ 0.6 W, 1 %, 50 ppm/K (e.g. Vishay MBB0207)","Vishay / Yageo","any distributor (0207 1 %)","0.08","0.08","estimate"
"yes","1","R51","Resistor","4.22 kΩ","power rating 250 mW","R_Axial_0207","metal film 4.22kΩ 0.6 W, 1 %, 50 ppm/K (e.g. Vishay MBB0207)","Vishay / Yageo","any distributor (0207 1 %)","0.08","0.08","estimate"
"yes","1","R52","Resistor","12.1 kΩ","power rating 250 mW","R_Axial_0207","metal film 12.1kΩ 0.6 W, 1 %, 50 ppm/K (e.g. Vishay MBB0207)","Vishay / Yageo","any distributor (0207 1 %)","0.08","0.08","estimate"
"yes","6","RV1 RV2 RV3 RV4 RV5 RV6","Varistor (MOV)","TMOV14RP300E","","TMOV_14","TMOV14RP300E","Littelfuse","Digi-Key; Mouser","1.60","9.60","estimate"
"yes","3","RV7 RV8 RV9","Potentiometer","","power rating 500 mW; wiper position 64%","Pot_Trimmer_3","3296W-1-502LF","Bourns","Mouser; Digi-Key","1.90","5.70","estimate"
"yes","2","T1 T2","Transformer","0.13","primary inductance 20 H; coupling 0.995; primary resistance 140 Ω; secondary resistance 1.5 Ω","Transformer_Wires_P7.62","FL 24/24 (or Hahn BV EI 482 series)","Block / Hahn","Bürklin / Reichelt","22.00","44.00","estimate"
"yes","3","T3 T4 T5","Transformer","0.052","primary inductance 100 H; coupling 0.99; primary resistance 2 kΩ; secondary resistance 20 Ω","Transformer_Wires_P7.62","VB 1,0/1/12","Block","RS 074-8411","7.20","21.60","live"
"yes","1","U1","Adjustable regulator","LM317HV","heatsink (case to air) 8 K/W","TO-220_Vertical","LM317HVT/NOPB","Texas Instruments","Mouser 926-LM317HVT/NOPB; RS 197-7244","2.20","2.20","live"
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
